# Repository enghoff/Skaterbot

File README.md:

# Skaterbot

Skaterbot is a 36 cm robot that stands on two legs and rolls on inline-skate
wheels. It is 3D-printed, weighs about 2 kg, and keeps itself upright with a small
neural network that learned to balance in simulation before it ever touched a real
floor.

<p align="center">
  
</p>
<p align="center"><a href="https://youtube.com/shorts/mM_8cwL3qOs">Watch the clip on YouTube</a> (15 seconds, filmed 6 November 2026)</p>

Nobody wrote down how to balance. The robot's six motors are driven by what the
network worked out for itself, falling over again and again in simulation, and the
same network then runs on the real machine. The project was called Biped until
November 2026, and the old word survives in names that code or the running robot
depends on.

## What it does

- **Balances on two wheels.** It stands and drives with nothing holding it up,
  deciding what all six motors should do 100 times a second.
- **Drives from an Xbox controller.** A full pull settles at about 1.5 m/s
  forwards, a brisk walk, and reversing is capped at the same speed. It turns as
  it goes, and learns how much steering it takes to hold a straight line.
- **Changes height.** Its legs fold, and the D-pad sets how tall it rides, between
  318 and 356 mm.
- **Jumps.** Hold A to crouch and let go to jump. In one session of 24 jumps, the
  wheels typically cleared the floor by 37 mm and it landed every time. That height
  is worked out from the logged joint angles, not filmed against a scale.

It first stood on its own on 5 November 2026, and was jumping three days later.

*Drawn from the CAD at heights the real robot uses. The orange parts are the
printed ones, which are black on the real robot.*

## What's inside

The robot began as an eight-motor walking design. Swapping its feet for wheels
removed the ankles and the sideways hip joints, and left two joints and a wheel on
each leg.

| Part | Role |
|---|---|
| Six [DAMIAO DM-J3507-2EC](reference/motors/README.md) motors | One at each hip and knee and one on each wheel, 165 g each. Their low gearing lets the joints give under load instead of fighting it. |
| 3D-printed frame | Torso, thighs and shins, printed in PLA. Each leg is 105 mm from hip to knee and 105 mm from knee to axle. |
| Two 80 mm inline-skate wheels | Ordinary polyurethane skate wheels with their bearings taken out. They are 170 mm apart where they meet the floor. |
| Banana Pi BPI-M4 Zero | The computer. Runs the neural network, reads the Xbox controller over Bluetooth and serves a diagnostics page to a browser. |
| Controller board (our own design) | A small microcontroller that links the computer to the motors, on three CAN buses, and to the sensors. |
| Power board (our own design) | The main fuse, the electronic on/off switch and a bank of capacitors. |
| BNO085 motion sensor | Tells the network which way is up and how fast the body is turning. |
| Two 3S LiPo packs in series | 1000 mAh at about 24 V, with a battery protection board. |

On a scale, the finished robot weighs **2,086 g**. With its legs straight it stands
363 mm tall. A rough planning figure for the parts is US$850 to US$1,200. That is
an estimate and not a record of what was spent, and the motors are the largest part
of it.

## How it stays up

![A diagram of the control loop. Every 10 milliseconds the Banana Pi reads 25 numbers from the motion sensor, the motors, the Xbox controller and its own last commands. A neural network turns them into four leg angles and two wheel torques, which go through the controller board to the motors. The robot moves and the sensors feel it, closing the loop.](docs/images/how-it-balances.svg)

A robot on two wheels is always falling and catching itself. Each cycle the network
sees how the body is tilted and turning, where the legs are, how fast the wheels
spin and what the driver wants, and answers with six numbers. Two are wheel
torques, which do most of the catching. Four are target angles for the hips and
knees, and each of those motors then holds its target with its own much faster loop
until the next answer arrives.

## How it learned

The network is trained by reinforcement learning (PPO), in NVIDIA Isaac Lab. Every
simulated robot is scored on staying up and doing what it is told, and thousands of
them practise at once. A run takes one to two hours on a single rented GPU.

A network that is perfect in simulation usually fails on real hardware, because
real motors weaken at speed, signals arrive late and printed parts are not quite
what was drawn. So the orange arrow matters most. Joint friction, leg weight, how
strong the wheel motors really are at speed and how late each signal arrives were
all measured on the robot itself and put into the simulator. The simulator then
varies what cannot be known exactly, such as sensor delay, wheel strength and where
the centre of mass sits, so that the network cannot come to depend on any one value.

## Designed as code, checked like code

Every part of Skaterbot is a Python function, written in
[build123d](https://build123d.readthedocs.io). That means the design can be tested
automatically. Nine sets of checks measure the holes, clearances and wall
thicknesses on the finished shapes, and walk the torso together in build order to
prove each part has a way in. The simulated robot is generated from the same code,
so its dimensions cannot drift away from the real one.

Most of those checks exist because something real went wrong:

- **The first printed torso came back without its floor posts.** The file held 22
  separate bodies, 16 of which only touched the shell, and the printer never joined
  them. Every printed piece must now be a single solid, and a check reads back the
  file a printer would receive.
- **The lid could not be fitted**, because its locating lip sat on its own screw
  bosses. Every part is now measured against every other.
- **The battery bay was drawn for a size nobody makes.** Bought parts are now
  recorded with where their dimensions came from.
- **All four hip arms broke off the second printed torso**, where they met its
  floor, so they are now braced.

## Current limits

This is a working prototype and it changes week to week.

- **The legs flex.** Under load the printed legs splay outwards into an A, so a
  rubber band between the shins holds them straight until stiffer ones are printed.
- **The wheels can work loose.** The screw that holds each wheel can back out and
  let it slip, which looks exactly like a control fault.
- **The jump is scripted, not learned.** Networks trained to jump failed on the real
  robot. Even the scripted jump ends in a fall about one time in thirty.
- **It has only been driven indoors on flat floors.** Rough ground and recovering
  from a shove have been tested only in simulation.
- **It cannot see.** There are no cameras or obstacle sensors, so it goes where it
  is driven.
- **Battery life has not been measured.** The longest logged run is about 12 minutes.

## Try it

Everything below is free and runs on an ordinary computer, with no robot needed.
It needs [uv](https://docs.astral.sh/uv/), which fetches everything else by itself.

```bash
git clone https://github.com/enghoff/Skaterbot
cd Skaterbot

# Drive the robot in simulation, with a keyboard or game controller
uv run simulation/mujoco/drive.py --run policies/rough-2026-11-05_10-37-59_fresh2_18

# Build every part and check it
uv run tools/check.py

# Add up the design's weight
uv run tools/mass.py

# Write the printable parts out as STEP files
uv run tools/export.py
```

There is no step-by-step build guide yet. The [bill of materials](docs/BOM.md)
lists what went into this robot.

## Explore the project

| Area | Contains |
|---|---|
| [`cad/`](cad/) and [`tools/`](tools/) | The robot's design as code, and the checks it is held to |
| [`simulation/`](simulation/README.md) | How the CAD becomes a simulated robot, and how much of it has been measured |
| [`simulation/isaaclab/`](simulation/isaaclab/README.md) | Training, and the [history of every training run](simulation/isaaclab/TRAINING_HISTORY.md) |
| [`policies/`](policies/README.md) | The trained networks the robot has run |
| [`sbc/`](sbc/) | What runs on the Banana Pi, including the [motor console](sbc/motor_console/README.md) |
| [`firmware/`](firmware/) | The controller board's firmware, in Rust |
| [`electrical/`](electrical/) | Both circuit boards, drawn and checked by script ([controller](docs/CARRIER.md), [power](docs/POWER_SWITCH.md)) |
| [`docs/`](docs/) | The [engineering log](docs/NOTES.md), [motor and system tests](docs/SYSID.md), and the [network's inputs and outputs](docs/POLICY_INTERFACE.md) |

To change the robot, start with [`docs/DEVELOPING.md`](docs/DEVELOPING.md).

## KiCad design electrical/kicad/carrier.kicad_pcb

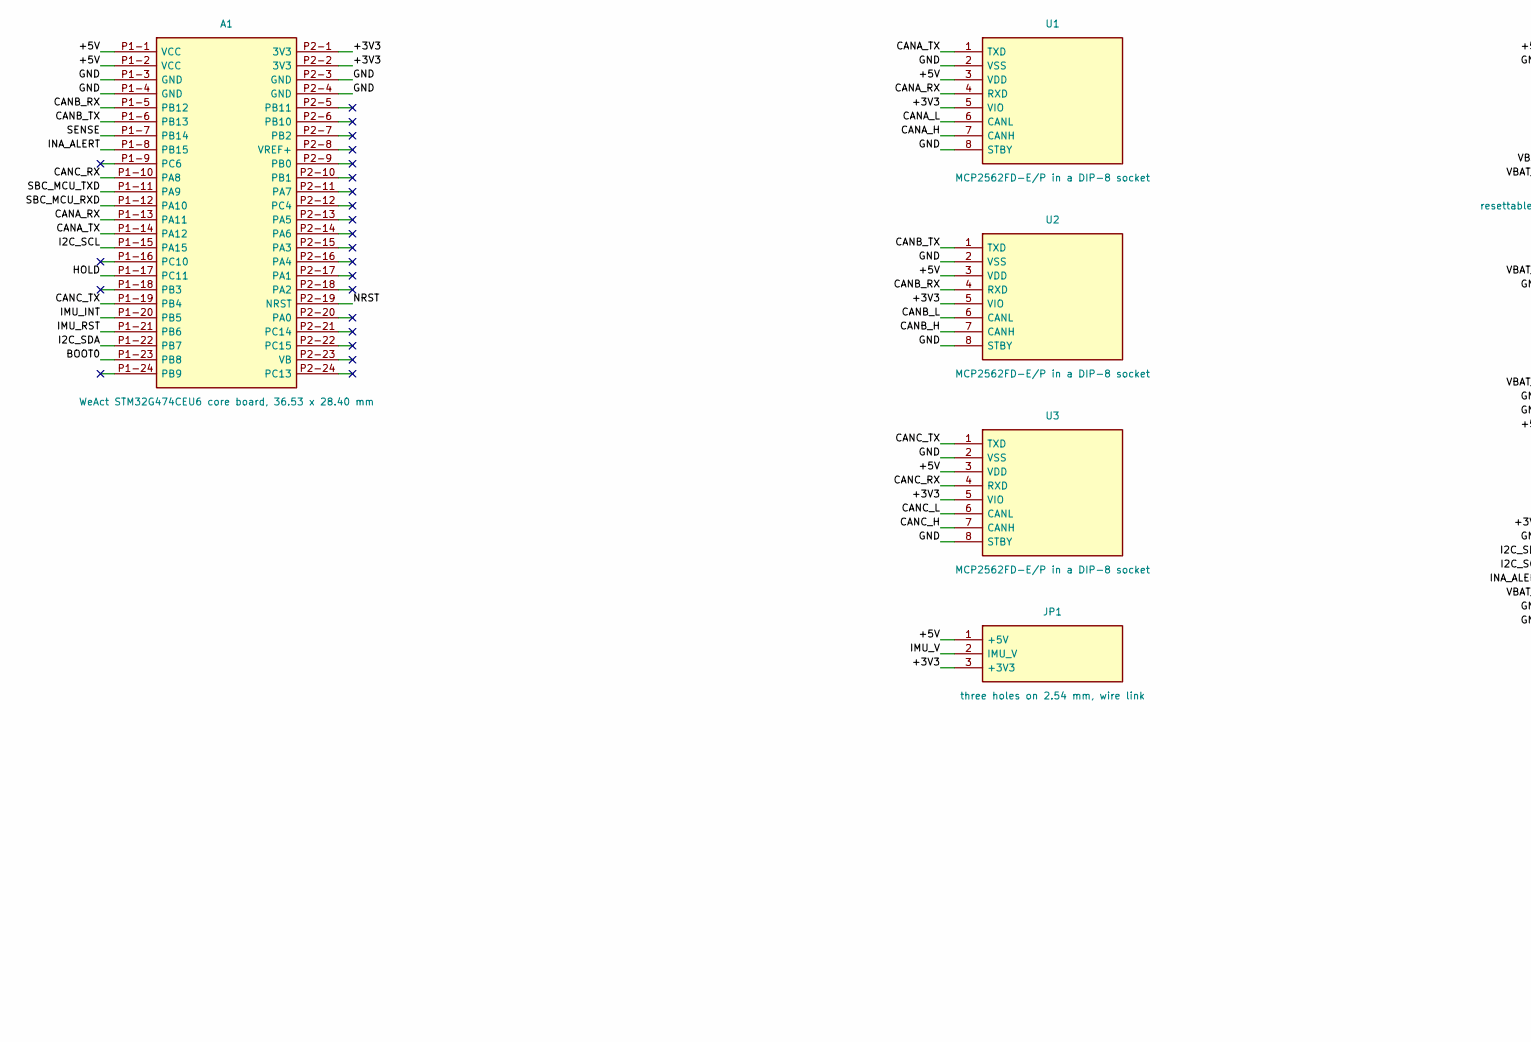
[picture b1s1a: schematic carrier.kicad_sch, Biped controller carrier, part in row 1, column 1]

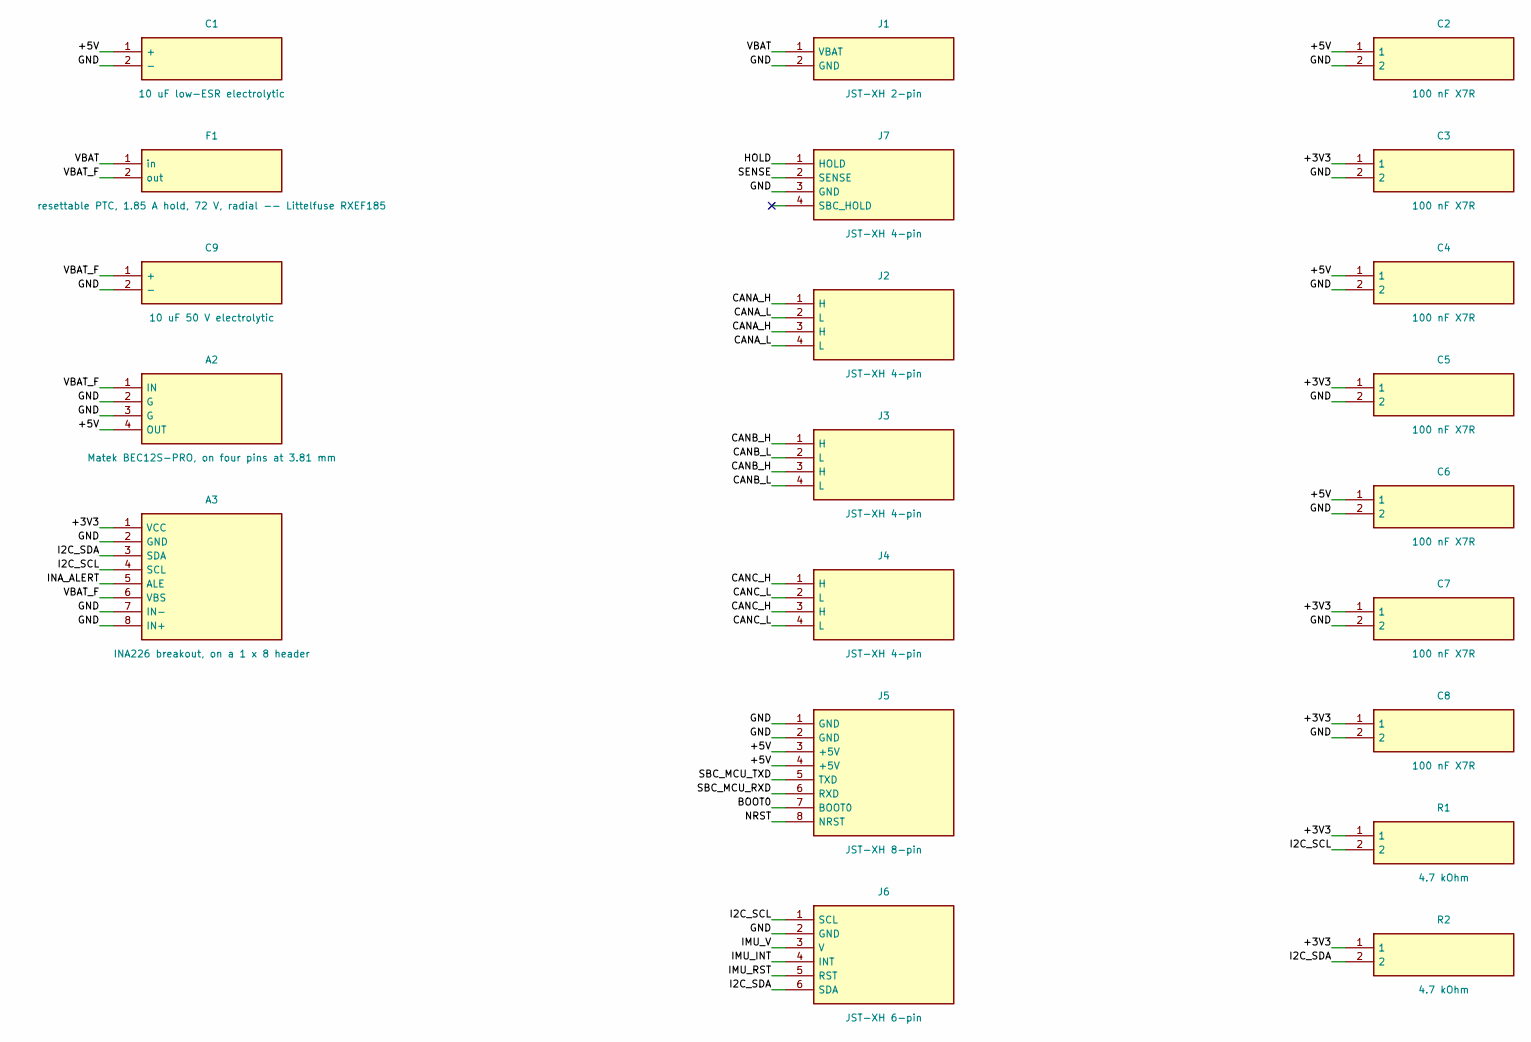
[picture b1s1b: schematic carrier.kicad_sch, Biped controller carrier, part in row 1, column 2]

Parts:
A1: WeAct STM32G474CEU6 core board, 36.53 x 28.40 mm; A1
A2: Matek BEC12S-PRO, on four pins at 3.81 mm; A2
A3: INA226 breakout, on a 1 x 8 header; A3
C1: 10 uF low-ESR electrolytic; C1
C2: 100 nF X7R; C2
C3: 100 nF X7R; C3
C4: 100 nF X7R; C4
C5: 100 nF X7R; C5
C6: 100 nF X7R; C6
C7: 100 nF X7R; C7
C8: 100 nF X7R; C8
C9: 10 uF 50 V electrolytic; C9
F1: resettable PTC, 1.85 A hold, 72 V, radial -- Litt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; F1
J1: JST-XH 2-pin; J1
J2: JST-XH 4-pin; J2
J3: JST-XH 4-pin; J3
J4: JST-XH 4-pin; J4
J5: JST-XH 8-pin; J5
J6: JST-XH 6-pin; J6
J7: JST-XH 4-pin; J7
JP1: three holes on 2.54 mm, wire link; JP1
R1: 4.7 kOhm; R1
R2: 4.7 kOhm; R2
U1: MCP2562FD-E/P in a DIP-8 socket; U1
U2: MCP2562FD-E/P in a DIP-8 socket; U2
U3: MCP2562FD-E/P in a DIP-8 socket; U3

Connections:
/+3V3: A1.P2-1 (3V3), A1.P2-2 (3V3), A3.1 (VCC), C3.1, C5.1, C7.1, C8.1, JP1.3 (+3V3), R1.1, R2.1, U1.5 (VIO), U2.5 (VIO), U3.5 (VIO)
/+5V: A1.P1-1 (VCC), A1.P1-2 (VCC), A2.4 (OUT), C1.1 (+), C2.1, C4.1, C6.1, J5.3 (+5V), J5.4 (+5V), JP1.1 (+5V), U1.3 (VDD), U2.3 (VDD), U3.3 (VDD)
/BOOT0: A1.P1-23 (PB8), J5.7 (BOOT0)
/CANA_H: J2.1 (H), J2.3 (H), U1.7 (CANH)
/CANA_L: J2.2 (L), J2.4 (L), U1.6 (CANL)
/CANA_RX: A1.P1-13 (PA11), U1.4 (RXD)
/CANA_TX: A1.P1-14 (PA12), U1.1 (TXD)
/CANB_H: J3.1 (H), J3.3 (H), U2.7 (CANH)
/CANB_L: J3.2 (L), J3.4 (L), U2.6 (CANL)
/CANB_RX: A1.P1-5 (PB12), U2.4 (RXD)
/CANB_TX: A1.P1-6 (PB13), U2.1 (TXD)
/CANC_H: J4.1 (H), J4.3 (H), U3.7 (CANH)
/CANC_L: J4.2 (L), J4.4 (L), U3.6 (CANL)
/CANC_RX: A1.P1-10 (PA8), U3.4 (RXD)
/CANC_TX: A1.P1-19 (PB4), U3.1 (TXD)
/GND: A1.P1-3 (GND), A1.P1-4 (GND), A1.P2-3 (GND), A1.P2-4 (GND), A2.2 (G), A2.3 (G), A3.2 (GND), A3.7 (IN-), A3.8 (IN+), C1.2 (-), C2.2, C3.2, C4.2, C5.2, C6.2, C7.2, C8.2, C9.2 (-), J1.2 (GND), J5.1 (GND), J5.2 (GND), J6.2 (GND), J7.3 (GND), U1.2 (VSS), U1.8 (STBY), U2.2 (VSS), U2.8 (STBY), U3.2 (VSS), U3.8 (STBY)
/HOLD: A1.P1-17 (PC11), J7.1 (HOLD)
/I2C_SCL: A1.P1-15 (PA15), A3.4 (SCL), J6.1 (SCL), R1.2
/I2C_SDA: A1.P1-22 (PB7), A3.3 (SDA), J6.6 (SDA), R2.2
/IMU_INT: A1.P1-20 (PB5), J6.4 (INT)
/IMU_RST: A1.P1-21 (PB6), J6.5 (RST)
/IMU_V: J6.3 (V), JP1.2 (IMU_V)
/INA_ALERT: A1.P1-8 (PB15), A3.5 (ALE)
/NRST: A1.P2-19 (NRST), J5.8 (NRST)
/SBC_MCU_RXD: A1.P1-12 (PA10), J5.6 (RXD)
/SBC_MCU_TXD: A1.P1-11 (PA9), J5.5 (TXD)
/SENSE: A1.P1-7 (PB14), J7.2 (SENSE)
/VBAT: F1.1 (in), J1.1 (VBAT)
/VBAT_F: A2.1 (IN), A3.6 (VBS), C9.1 (+), F1.2 (out)

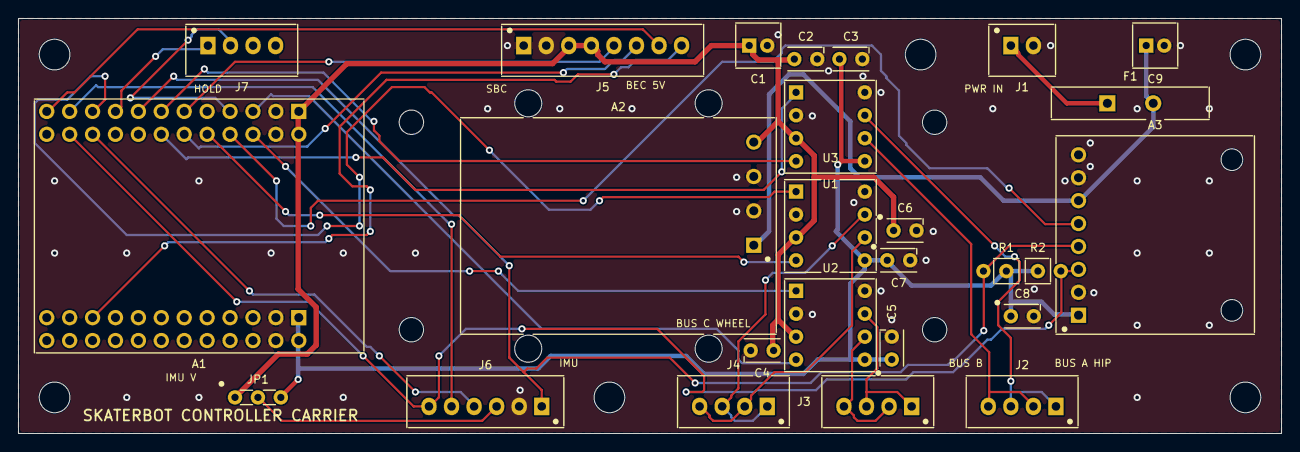
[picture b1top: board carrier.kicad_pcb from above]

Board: 2 copper layers, 140.0 x 46.0 mm, 36 parts (0 on the bottom side), 29 nets.

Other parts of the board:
H_MountingHole_M3_1: MountingHole_M3_1
H_MountingHole_M3_2: MountingHole_M3_2
H_MountingHole_M3_3: MountingHole_M3_3
H_MountingHole_M3_4: MountingHole_M3_4
H_MountingHole_M3_5: MountingHole_M3_5
H_MountingHole_M3_6: MountingHole_M3_6
H_SBC_Standoff_M2.5_1: SBC_Standoff_M2.5_1
H_SBC_Standoff_M2.5_2: SBC_Standoff_M2.5_2
H_SBC_Standoff_M2.5_3: SBC_Standoff_M2.5_3
H_SBC_Standoff_M2.5_4: SBC_Standoff_M2.5_4

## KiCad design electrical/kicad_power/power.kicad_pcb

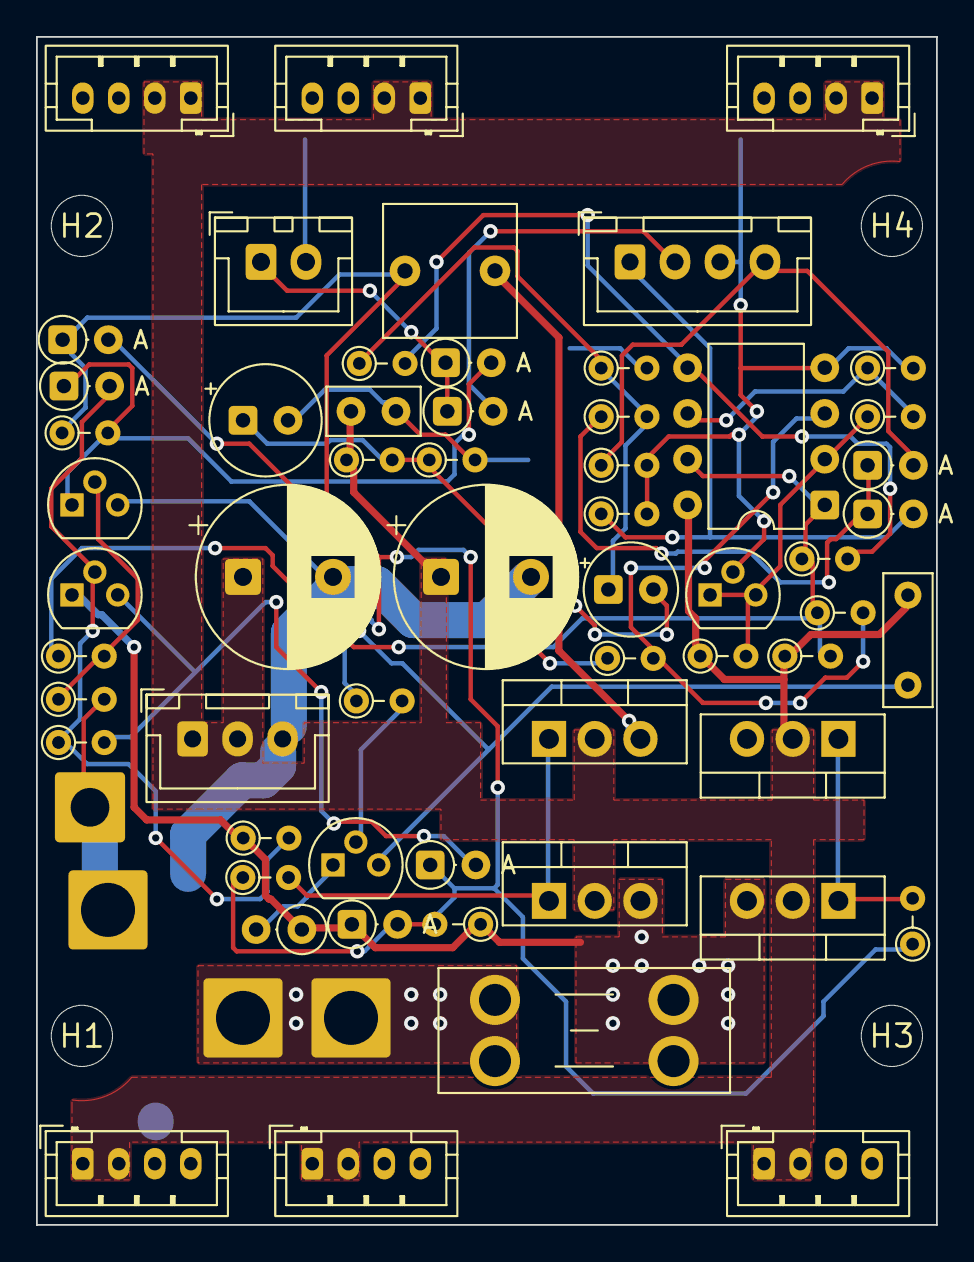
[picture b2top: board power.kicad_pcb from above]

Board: 2 copper layers, 50.0 x 66.0 mm, 66 parts (0 on the bottom side), 26 nets.

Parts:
C1: KEMET R82DC3220AA60K, 220 nF 63 V film, 5 mm pitch; C_Rect_L7.2mm_W2.5mm_P5.00mm
C2: KEMET C315C104K5R5TA, 100 nF 50 V X7R, 2.54 mm; C_Disc_D5.0mm_W2.5mm_P2.50mm
C3: 22 uF 16 V solid tantalum, radial; CP_Radial_Tantal_D6.0mm_P2.50mm
C4: 10 uF 16 V solid tantalum, radial; CP_Radial_Tantal_D5.0mm_P2.50mm
C5, C6: 470 uF 35 V low-ESR aluminium, 10 x 16 radial; CP_Radial_D10.0mm_P5.00mm
C7: KEMET MMK5225K63J06L4BULK, 2.2 uF 63 V 10 %, 5 mm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; C_Rect_L7.2mm_W7.2mm_P5.00mm
D1: BZX79-C15, 15 V 0.5 W zener, DO-35; D_DO-35_SOD27_P2.54mm_Vertical_AnodeUp
D2, D3, D4, D5, D6, D7, D8: 1N4148, DO-35; D_DO-35_SOD27_P2.54mm_Vertical_AnodeUp
F1: Keystone 3568 holder + mini (ATM) blade fuse, 20 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; Fuseholder_Blade_Mini_Keystone_3568
H1, H2, H3, H4: (no value)
J2: JST-XH 4-pin; JST_XH_B4B-XH-A_1x04_P2.50mm_Vertical
J3: JST-XH 2-pin; JST_XH_B2B-XH-A_1x02_P2.50mm_Vertical
J4, J5, J6, J7, J8, J9: JST-PH 4-pin; JST_PH_B4B-PH-K_1x04_P2.00mm_Vertical
J10: JST-XH 3-pin; JST_XH_B3B-XH-A_1x03_P2.50mm_Vertical
P1, P3, P5: wire pad, 3.0 mm hole; SolderWire-2.5sqmm_1x01_D2.4mm_OD4.4mm
P4: wire pad, 2.15 mm hole; SolderWire-1.5sqmm_1x01_D1.7mm_OD3.9mm
Q1, Q2, Q6, Q7: Infineon IRF4905PbF, P-channel 55 V, TO-220AB; TO-220-3_Vertical
Q3, Q4, Q5: BC546B NPN 65 V, TO-92; TO-92
R2, R9: 1 MOhm, 0204 metal film; R_Axial_DIN0204_L3.6mm_D1.6mm_P2.54mm_Vertical
R3, R4: 10 Ohm, 0204 metal film; R_Axial_DIN0204_L3.6mm_D1.6mm_P2.54mm_Vertical
R5: 470 kOhm, 0204 metal film; R_Axial_DIN0204_L3.6mm_D1.6mm_P2.54mm_Vertical
R6, R8, R15: 47 kOhm, 0204 metal film; R_Axial_DIN0204_L3.6mm_D1.6mm_P2.54mm_Vertical
R7, R16, R17, R19: 100 kOhm, 0204 metal film; R_Axial_DIN0204_L3.6mm_D1.6mm_P2.54mm_Vertical
R10: 15 kOhm, 0204 metal film; R_Axial_DIN0204_L3.6mm_D1.6mm_P2.54mm_Vertical
R11, R22, R23: 100 kOhm 1 %, 0204 metal film; R_Axial_DIN0204_L3.6mm_D1.6mm_P2.54mm_Vertical
R12: 15 kOhm 1 %, 0204 metal film; R_Axial_DIN0204_L3.6mm_D1.6mm_P2.54mm_Vertical
R13, R20: 22 kOhm, 0204 metal film; R_Axial_DIN0204_L3.6mm_D1.6mm_P2.54mm_Vertical
R14, R21: 10 MOhm, 0204 metal film; R_Axial_DIN0204_L3.6mm_D1.6mm_P2.54mm_Vertical
R18: 1 kOhm, 0204 metal film; R_Axial_DIN0204_L3.6mm_D1.6mm_P2.54mm_Vertical
R25: 10 kOhm, 0204 metal film; R_Axial_DIN0204_L3.6mm_D1.6mm_P2.54mm_Vertical
R26: 1 kOhm 1 W, PR01 axial; R_Axial_DIN0207_L6.3mm_D2.5mm_P2.54mm_Vertical
U1: LM393P, DIP-8; DIP-8_W7.62mm
U2: TL431ACLP, TO-92; TO-92

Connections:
BATT: F1.1, P1.1, P5.1
BTN: D6.1, D7.1, J3.1
EN: R6.1, R14.1, R15.2, R21.1, U1.1, U1.7
EN_B: Q3.2, R6.2, R7.1
FAST_B: D3.2, Q4.2, R8.2, R9.1
FAST_E: D2.2, Q4.3, R9.2
G1: Q1.1, Q6.1, R3.2
G2: Q2.1, Q7.1, R4.2
GATE: C7.2, D1.2, D2.1, D8.1, R2.2, R3.1, R4.1, R5.1, R25.1
GND: C2.2, C3.2, C4.2, C5.2, C6.2, J2.3, J3.2, J4.3, J4.4, J5.3, J5.4, J6.3, J6.4, J7.3, J7.4, J8.3, J8.4, J9.3, J9.4, J10.3, P3.1, P4.1, Q3.3, R7.2, R12.2, R16.2, R17.2, R19.2, R23.2, U1.4, U2.2
HOLD_CAP: C4.1, R18.2, R19.1, R20.1
HOLD_IN: R20.2, R21.2, U1.5
HOLD_MCU: D4.2, J2.1, R16.1
HOLD_OR: D4.1, D5.1, R18.1
HOLD_REF: R22.2, R23.1, U1.6
HOLD_SBC: D5.2, J2.4, R17.1
MILLER: C1.1, D8.2, Q5.3
PULL: D3.1, D6.2, Q3.1, R5.2
REF: R10.2, R22.1, U1.2, U2.1, U2.3
RESET_B: Q5.2, R25.2
RESET_C: Q5.1, R26.2
SENSE: D7.2, J2.2
UV_DIV: C3.1, R11.2, R12.1, R13.1
UV_IN: R13.2, R14.2, U1.3
VBUS: C1.2, C2.1, C5.1, C6.1, J4.1, J4.2, J5.1, J5.2, J6.1, J6.2, J7.1, J7.2, J8.1, J8.2, J9.1, J9.2, J10.1, J10.2, Q1.2, Q2.2, Q6.2, Q7.2, R10.1, R11.1, R15.1, U1.8
VSRC: C7.1, D1.1, F1.2, Q1.3, Q2.3, Q4.1, Q6.3, Q7.3, R2.1, R8.1, R26.1

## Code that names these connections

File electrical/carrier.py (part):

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#
# WHICH BOARD THIS IS MATTERS, and docs/BOM.md currently names two of them. Its
# purchase link points at WeAct's LONG type, a different board -- 63.06 x 18.24
# mm, two 1 x 20 headers, and PB8 not brought out to a header at all -- while
# its quoted dimension, its header note and cad/electronics.py all describe this
# one. This file is drawn to the board the CAD packs. docs/CARRIER.md has it.

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    2: "VCC",
    3: "GND",
    4: "GND",
    5: "PB12",
    6: "PB13",
    7: "PB14",
    8: "PB15",
    9: "PC6",
    10: "PA8",
    11: "PA9",
    12: "PA10",
    13: "PA11",
    14: "PA12",
    15: "PA15",
    16: "PC10",
    17: "PC11",
    18: "PB3",
    19: "PB4",
    20: "PB5",
    21: "PB6",
    22: "PB7",
    23: "PB8",
    24: "PB9",
}

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# an assignment below a claim rather than a hope.

AF_TABLE = {
    "FDCAN1_RX": ("PA11", "PB8"),
    "FDCAN1_TX": ("PA12", "PB9"),
    "FDCAN2_RX": ("PB5", "PB12"),
    "FDCAN2_TX": ("PB6", "PB13"),
    "FDCAN3_RX": ("PA8", "PB3"),
    "FDCAN3_TX": ("PA15", "PB4"),
    "I2C1_SCL": ("PA13", "PA15", "PB8"),
    "I2C1_SDA": ("PA14", "PB7", "PB9"),
    "USART1_TX": ("PA9", "PB6"),
    "USART1_RX": ("PA10", "PB7"),
    "SYS": ("PB8", "NRST"),
}

# Pins whose reset state is a JTAG function. The debugger is SWD, which needs
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# is the safe direction for both of them: a CAN TXD pulled high is recessive,
# and an I2C clock pulled high is idle. PB3 is left unused on purpose so that
# SWO tracing still has a pin.
JTAG_AT_RESET = ("PA15", "PB3", "PB4")


@dataclass(frozen=True)
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    # THE POWER SWITCH BOARD'S HOLD AND BUTTON, 2026-10-07, which had nowhere to
    # land on this board since that board was drawn. Four pins in the order its
    # own J2 has them, so one ready-made lead runs straight between the two:
    # the MCU's hold out, the button back in, ground -- and on pin 4 the SBC's
    # hold, which passes this board by and leaves the lead for the SBC's 40-pin
    # header before it gets here. FOUR AND NOT THREE because the power switch
    # board's feed to J1 leaves that board on a three-pin plug, and a plug that
    # carries the bus must not fit a socket wired to the MCU.
    Part(
        "J7",
        "the power switch board's hold lead: the MCU's hold out, the button back "
        "in, ground; pin 4 is the SBC's hold and is not used here",
        "JST-XH 4-pin",
        {"1": "HOLD", "2": "SENSE", "3": "GND", "4": "SBC_HOLD"},
    ),
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# pin it comes out on. check() holds all four against each other and against
# AF_TABLE, so a pin that cannot do its job fails here rather than on the bench.
#
# BUS A IS ON PA11/PA12 AND NOT ON PB8/PB9, which is the one place this differs
# from the arrangement docs/BOM.md describes, and the reason is a power-up race
# rather than a preference. PB8 is the BOOT0 pin. A transceiver's RXD idles high
# on a quiet bus, so wiring RXD to PB8 means the level the MCU samples to decide
# where to boot from is whatever the transceiver happens to be doing at that
# instant -- flash if the 5 V rail is still below the transceiver's 4 V
# undervoltage threshold, the system bootloader if it is not. The cure is to
# take the boot source off the pin in the option bytes, which works, but it is a
# step that has to be done before the robot will start at all and it cannot be
# undone without a debugger. Putting bus A on PA11/PA12 costs the core board's
# USB instead, and nothing in this robot uses it: the SBC link is serial and the
# programmer is SWD.

MCU_SIGNALS = [
    ("CANA_TX", "PA12", "FDCAN1_TX", "P1-14"),
    ("CANA_RX", "PA11", "FDCAN1_RX", "P1-13"),
    ("CANB_TX", "PB13", "FDCAN2_TX", "P1-6"),
    ("CANB_RX", "PB12", "FDCAN2_RX", "P1-5"),
    ("CANC_TX", "PB4", "FDCAN3_TX", "P1-19"),
    ("CANC_RX", "PA8", "FDCAN3_RX", "P1-10"),
    ("I2C_SCL", "PA15", "I2C1_SCL", "P1-15"),
    ("I2C_SDA", "PB7", "I2C1_SDA", "P1-22"),
    ("SBC_MCU_TXD", "PA9", "USART1_TX", "P1-11"),
    ("SBC_MCU_RXD", "PA10", "USART1_RX", "P1-12"),
    ("IMU_INT", "PB5", "GPIO", "P1-20"),
    ("IMU_RST", "PB6", "GPIO", "P1-21"),
    ("INA_ALERT", "PB15", "GPIO", "P1-8"),
    # The power switch board's hold and button, 2026-10-07: two of the spare
    # pins on the core board's front row, beside the plug they come in on. NOT
    # PC6, which is next to PB14 and free on the header but carries the core
    # board's own blue LED -- firmware/policy blinks it.
    ("HOLD", "PC11", "GPIO", "P1-17"),
    ("SENSE", "PB14", "GPIO", "P1-7"),
    ("BOOT0", "PB8", "SYS", "P1-23"),
    ("NRST", "NRST", "SYS", "P2-19"),
]

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    12: ("PI1", "I2S0_BCLK"),
}

# THE SBC'S HOLD ON HEADER PIN 12, PI1, chosen 2026-10-17. It does not come
# through J5: it is pin 4 of the power switch board's hold lead, whose wire
# leaves that lead for this pin before it reaches J7, soldered like J5's. Pin 12 is
# the one plain port pin left in the block J5 already uses, and I2S0 is off.
#
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# debug header of its own, so this port is not the console. Whether the OS image
# brings UART4 up, or needs an overlay to, has not been checked.
#
# BOOT0 ON PI12 IS SAFE WHILE THE PI BOOTS. The core board holds PB8 low through
# its own 10 kOhm (R2 on reference/WeAct_STM32G474CoreBoard_SCH.pdf), so a Pi pin
# that floats until Linux claims it leaves the MCU booting from flash. The Pi
# drives it high only to drop the MCU into its ROM bootloader.
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# high. The core board's reset button shorts NRST to ground and the MCU pulls its
# own NRST low on a watchdog or brown-out reset, and a pin driven high fights
# both. Nothing else holds it up: the board's 10 kOhm pull-up (R3) is marked not
# fitted, so it is the MCU's internal pull-up and C2's 100 nF. PH2 is also
# UART5_TX, so UART5 stays off.
SBC_NEEDS = {
    "GND": "GND",
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            )
        taken[header] = pin

    # 7. The SBC's hold, on a plain port pin that J5 does not already take.
    names = BPI_HEADER.get(SBC_HOLD_HEADER)
    if names is None:
        faults.append(f"SBC_HOLD: header pin {SBC_HOLD_HEADER} is not in BPI_HEADER")
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        passiveY = (asideHeight - mcuHeight) / 2 - 2.4
        d += (
            elm.Label()
            .label("Decoupling and pull-ups", fontsize=11)
            .at((mcuLeft + 3.4, passiveY + 1.4))
        )
        for refdes, value, rail, sink, why in passives:
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
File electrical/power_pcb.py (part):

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    # reset line had to cut across the row: once the bus took the inboard column
    # those two were what was left unrouted in every order tried. D1 and R2 are
    # in parallel between the same two nets, so R26 and R2 turned end for end:
    # it reads RESET_C, VSRC, VSRC, GATE, GATE, VSRC now, the reset pin at the
    # end nearest Q5 and R2's source pin at the gap down to the source pour.
    "D1": (39.05, -16.3, 0),
    "R2": (46.2, -16.3, 180),
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        # ITS TOP EDGE CAME DOWN 0.7 mm, 2026-10-07, to -18.6, which still takes
        # in the fuse holder's pins and P1 whole: it leaves a lane under the row
        # of upright parts above it, the only way the source pins in that row
        # reach one another past the gate pins between them.
        # AND ITS BOTTOM EDGE WENT UP 0.6 mm, to -24.0, the same day, for the bus
        # bar to the rear strip's headers, which has to pass under it. P1 is
        # still whole inside it.
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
